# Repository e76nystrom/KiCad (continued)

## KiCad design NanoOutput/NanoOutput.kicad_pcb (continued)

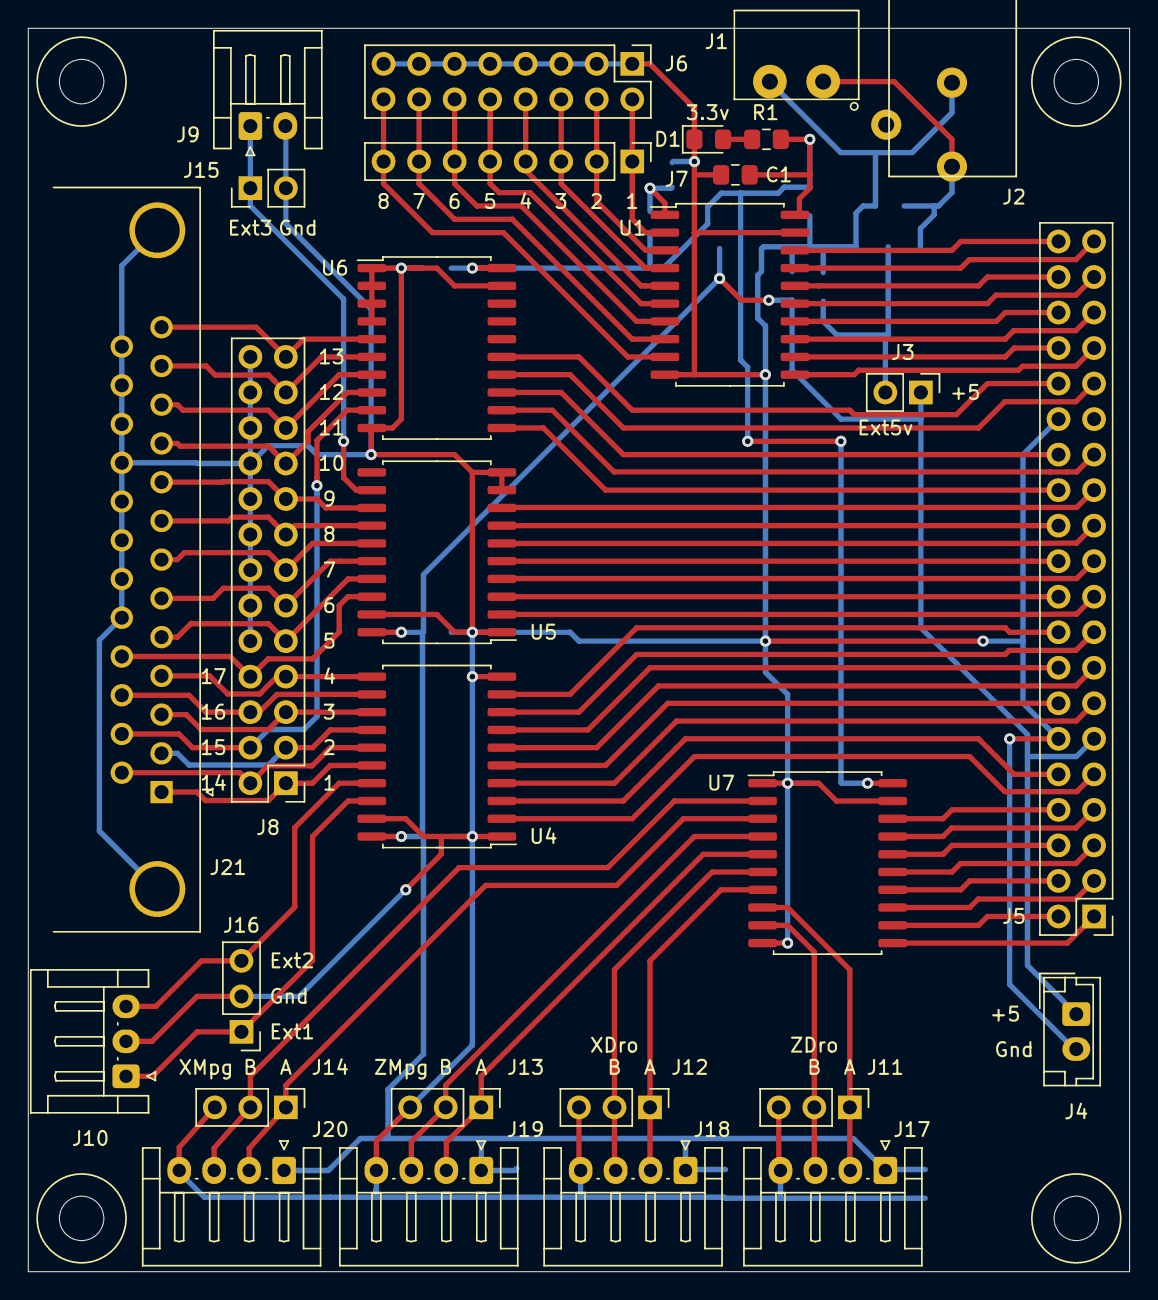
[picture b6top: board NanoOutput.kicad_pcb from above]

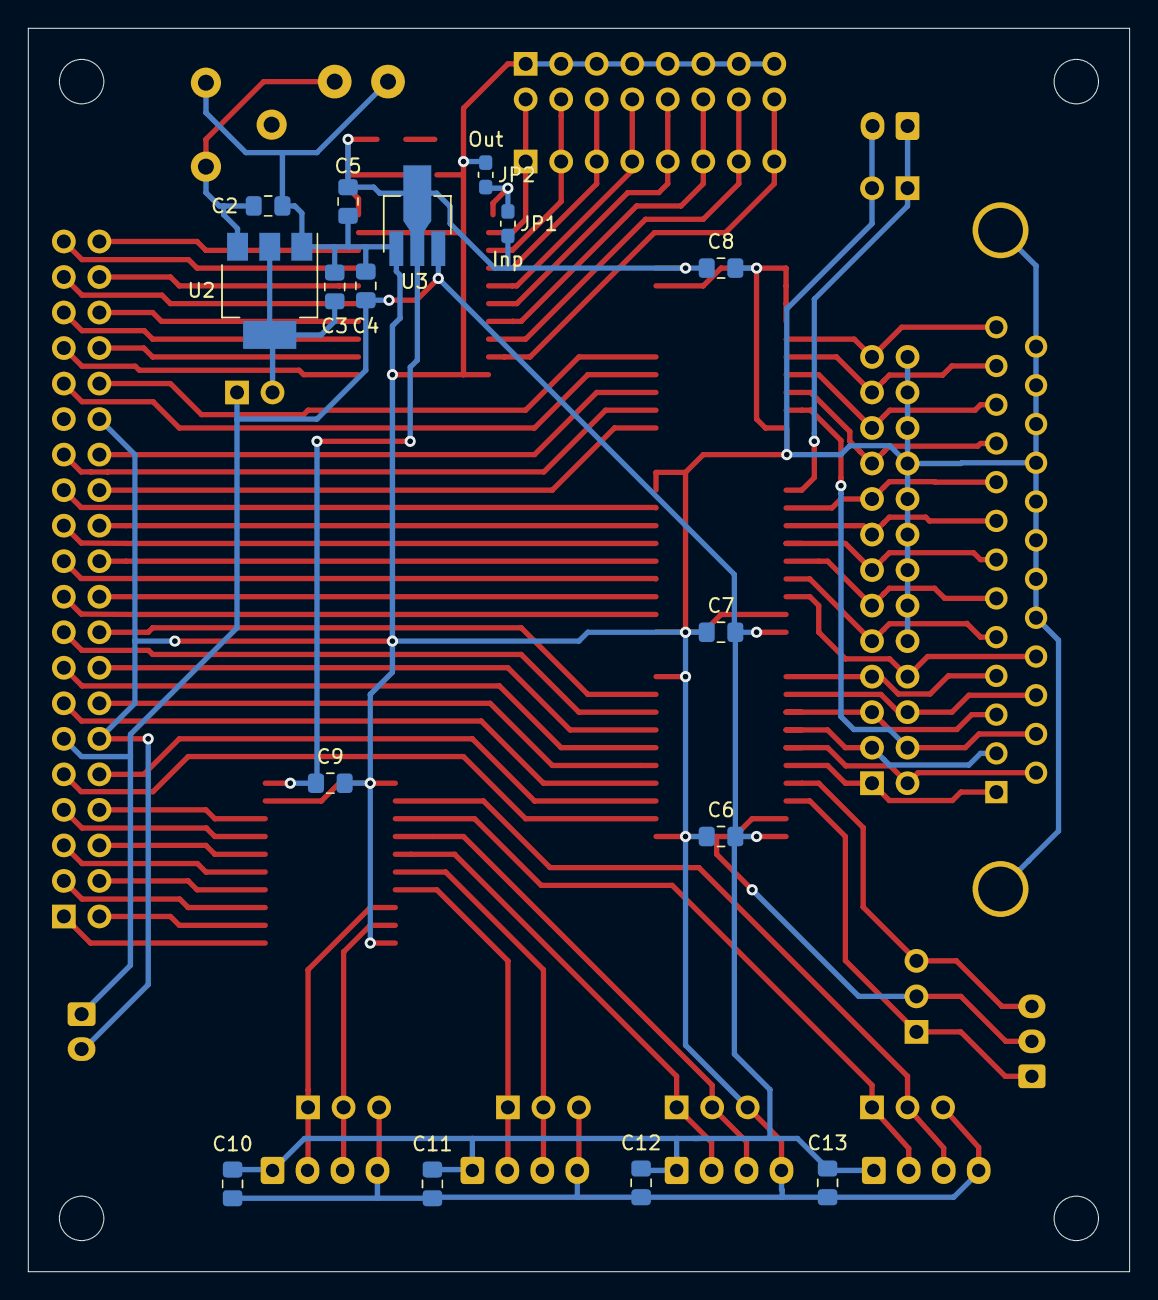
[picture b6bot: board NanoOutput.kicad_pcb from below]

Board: 2 copper layers, 78.7 x 88.9 mm, 49 parts (16 on the bottom side), 79 nets.

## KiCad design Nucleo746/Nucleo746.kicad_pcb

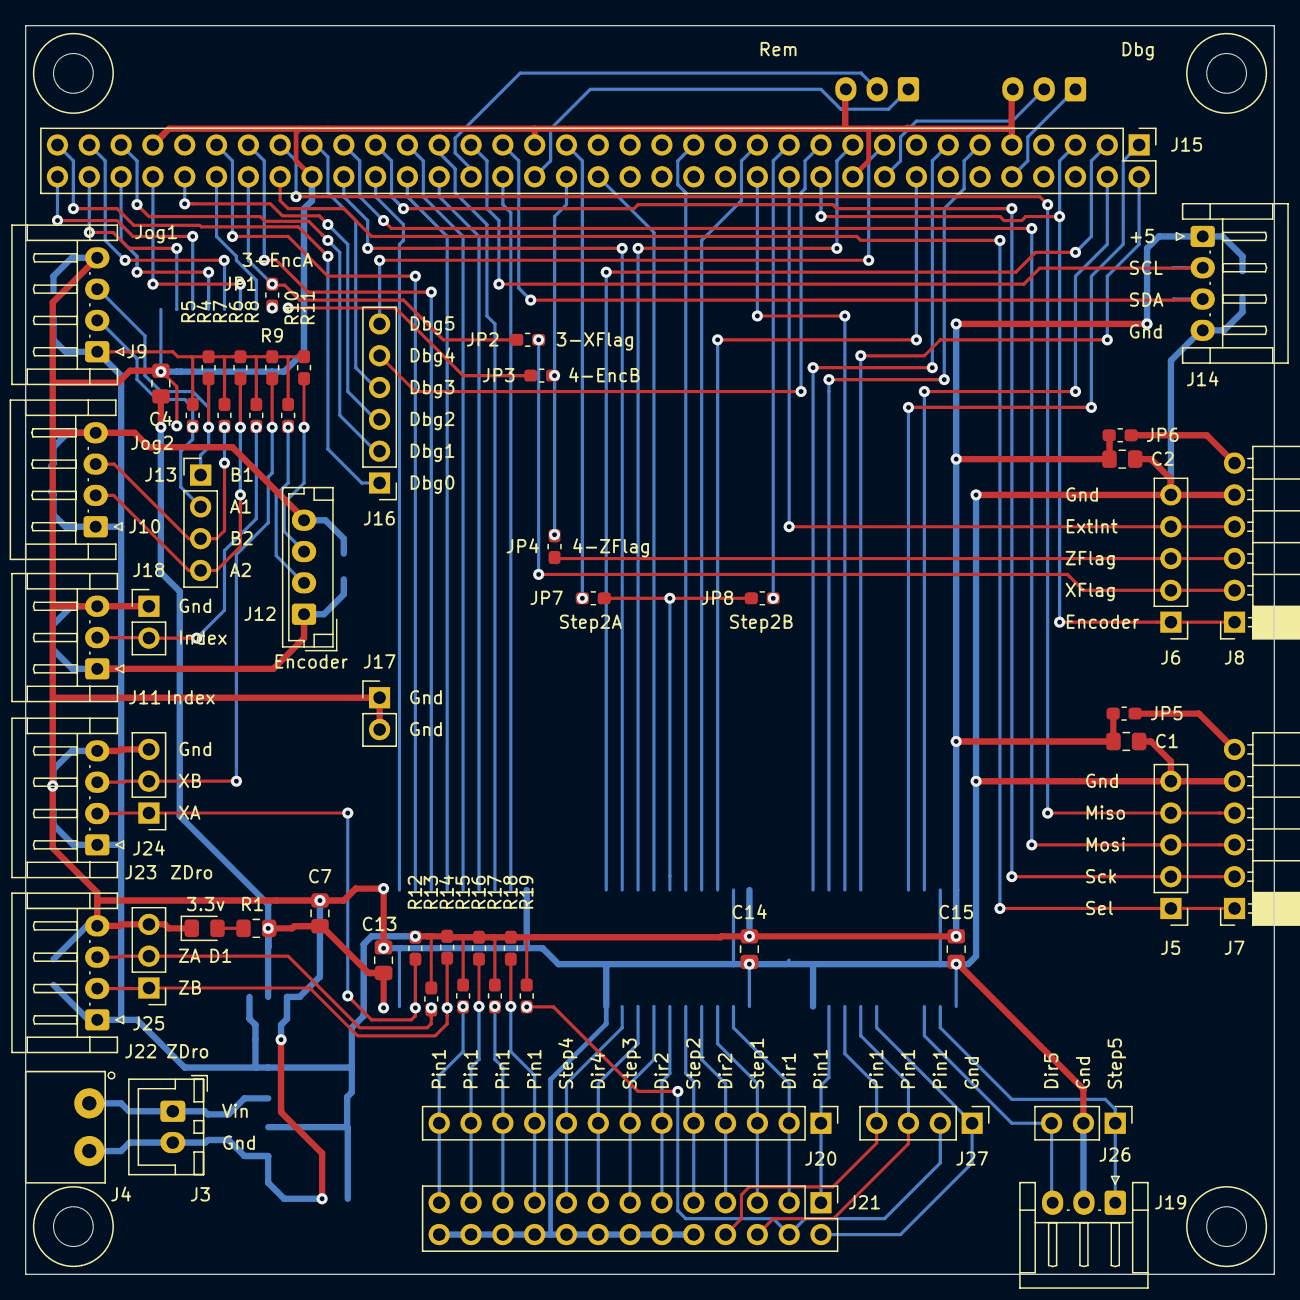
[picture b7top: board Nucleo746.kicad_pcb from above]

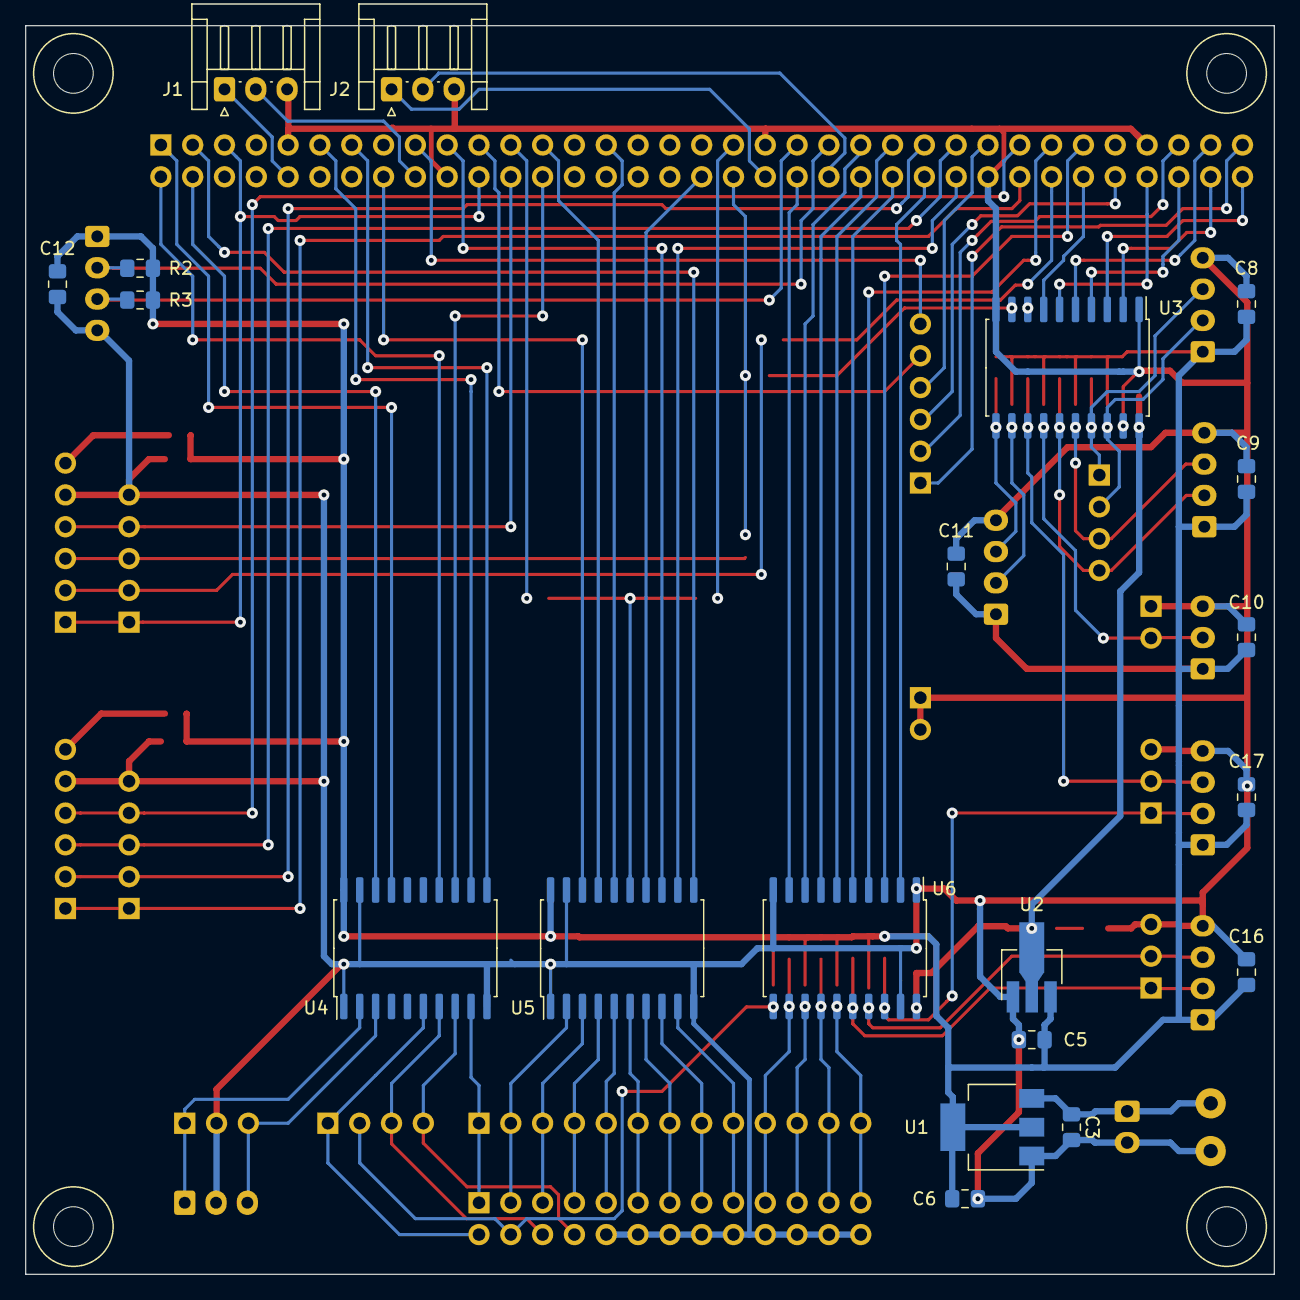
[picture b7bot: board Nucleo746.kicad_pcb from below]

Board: 2 copper layers, 99.7 x 99.7 mm, 82 parts (20 on the bottom side), 91 nets.

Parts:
C1, C2, C3, C4, C6, C8, C9, C10, C11, C12, C13, C14, C15, C16, C17: .1uf; C_0805_2012Metric_Pad1.15x1.40mm_HandSolder
C5, C7: 10uf; C_0805_2012Metric_Pad1.15x1.40mm_HandSolder
D1: LED; D_0805_2012Metric_Pad1.15x1.40mm_HandSolder
H1, H2, H3, H4: MountingHole; MountingHole _1-8_1-4
J1, J2, J11, J19: Conn_01x03; JST_EH_S3B-EH_1x03_P2.50mm_Horizontal
J3: Conn_01x02; JST_XH_B2B-XH-A_1x02_P2.50mm_Vertical
J4: Conn_01x02; 2 Pin 3.81mm
J5, J6: Conn_01x05_Male; PinHeader_1x05_P2.54mm_Vertical
J7, J8: Conn_01x06; PinSocket_1x06_P2.54mm_Horizontal
J9, J10, J14, J22, J23: Conn_01x04; JST_EH_S4B-EH_1x04_P2.50mm_Horizontal
J12: Conn_01x04; JST_EH_B4B-EH-A_1x04_P2.50mm_Vertical
J13, J27: Conn_01x04_Male; PinHeader_1x04_P2.54mm_Vertical
J15: N746Right; PinHeader_2x35_P2.54mm_Vertical
J16: Conn_01x06_Male; PinHeader_1x06_P2.54mm_Vertical
J17, J18: Conn_01x02_Male; PinHeader_1x02_P2.54mm_Vertical
J20: Conn_01x13_Male; PinHeader_1x13_P2.54mm_Vertical
J21: Conn_02x13_Top_Bottom; PinHeader_2x13_P2.54mm_Vertical
J24, J25, J26: Conn_01x03_Male; PinHeader_1x03_P2.54mm_Vertical
JP1, JP3, JP7: S2_T5; R_0603_1608Metric_Pad1.05x0.95mm_HandSolder
JP2, JP4, JP8: S2_T1; R_0603_1608Metric_Pad1.05x0.95mm_HandSolder
JP5, JP6: 5v; R_0603_1608Metric_Pad1.05x0.95mm_HandSolder
R1: R; R_0805_2012Metric_Pad1.15x1.40mm_HandSolder
R2, R3: 4.7k; R_0805_2012Metric_Pad1.15x1.40mm_HandSolder
R4, R5, R6, R7, R8, R9, R10, R11, R12, R13, R14, R15, R16, R17, R18, R19: 10k; R_0603_1608Metric_Pad1.05x0.95mm_HandSolder
U1: AMS1117-5.0; SOT-223-3_TabPin2
U2: AMS1117-3.3; SOT-89-3_Handsoldering
U3, U4, U5, U6: 74HC245; SOIC-20W_7.5x12.8mm_P1.27mm

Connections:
+3V3: C4.1, C7.1, C13.1, R1.1, U2.2, U3.20, U6.20
+5V: C1.1, C2.1, C5.1, C6.1, C8.1, C9.1, C10.1, C11.1, C12.1, C14.1, C15.1, C16.1, C17.1, J9.1, J10.1, J11.1, J12.1, J14.1, J22.1, J23.1, JP5.1, JP6.1, R2.1, R3.1, R4.1, R5.1, R6.1, R7.1, R8.1, R9.1, R10.1, R11.1, R12.1, R13.1, R14.1, R15.1, R16.1, R17.1, R18.1, R19.1, U1.2, U2.3, U4.20, U5.20
/5v1: J7.6, JP5.2
/5v2: J8.6, JP6.2
/Dbg0: J15.69, J16.1
/Dbg1: J15.65, J16.2
/Dbg2: J15.62, J16.3
/Dbg3: J15.53, J16.4
/Dbg4: J15.21, J16.5
/Dbg5: J15.17, J16.6
/Dir1: J15.16, U5.18
/Dir1Buf: J20.2, J21.2, U5.2
/Dir2: J15.29, U5.16
/Dir2Buf: J20.4, J21.4, U5.4
/Dir3: J15.36, U5.14
/Dir3Buf: J20.6, J21.6, U5.6
/Dir4: J15.52, U5.12
/Dir4Buf: J20.8, J21.8, U5.8
/Dir5: J15.1, U4.17
/Dir5Buf: J19.3, J26.3, U4.3
/EncA: J12.2, R10.2, U3.12
/EncABuf: JP1.1, U3.8
/EncB: J12.3, R11.2, U3.11
/EncBBuf: JP3.1, U3.9
/Encoder: J6.1, J8.1, J15.5, J15.22
/ExtInt: J6.4, J8.4, J15.24
/Exti3: J15.58, JP1.2, JP2.1
/Exti4: J15.38, JP3.2, JP4.1
/I2C_SCL: J14.2, J15.43, R2.2
/I2C_SDA: J14.3, J15.41, R3.2
/Index: J11.2, J18.2, R8.2, U3.14
/IndexBuf: J15.64, U3.6
/JogA1: J9.2, J13.2, R5.2, U3.18
/JogA1Buf: J15.68, U3.2
/JogA2: J10.2, J13.4, R6.2, U3.15
/JogA2Buf: J15.67, U3.5
/JogB1: J9.3, J13.1, R4.2, U3.17
/JogB1Buf: J15.70, U3.3
/JogB2: J10.3, J13.3, R7.2, U3.16
/JogB2Buf: J15.66, U3.4
/LedR: D1.2, R1.2
/Pin1: J15.13, U4.11
/Pin1Buf: J20.1, J21.1, U4.9
/Pin10: J20.10, J21.10, R18.2, U6.12
/Pin10Buf: J15.45, U6.8
/Pin11: J20.11, J21.11, R17.2, U6.13
/Pin11Buf: J15.46, U6.7
/Pin12: J20.12, J21.12, R16.2, U6.14
/Pin12Buf: J15.47, U6.6
/Pin13: J20.13, J21.13, R15.2, U6.15
/Pin13Buf: J15.48, U6.5
/Pin14: J15.2, U4.14
/Pin14Buf: J21.14, J27.1, U4.6
/Pin15: J21.15, J27.2, R19.2, U6.11
/Pin15Buf: J15.42, U6.9
/Pin16Buf: J21.16, J27.3, U4.7
/Pin17: J15.11, U4.12
/Pin17Buf: J21.17, J27.4, U4.8
/Pwm: J15.26, U4.13
/SPI_MISO: J5.4, J7.4, J15.55
/SPI_MOSI: J5.3, J7.3, J15.51
/SPI_SCK: J5.2, J7.2, J15.49
/SPI_SEL: J5.1, J7.1, J15.56
/Step1: J15.25, U5.17
/Step1Buf: J20.3, J21.3, U5.3
/Step2: JP7.2, JP8.1, U5.15
/Step2A: J15.37, JP7.1
/Step2B: J15.23, JP8.2
/Step2Buf: J20.5, J21.5, U5.5
/Step3: J15.19, U5.13
/Step3Buf: J20.7, J21.7, U5.7
/Step4: J15.3, U5.11
/Step4Buf: J20.9, J21.9, U5.9
/Step5: J15.4, U4.18
/Step5Buf: J19.1, J26.1, U4.2
/Uart3Rx: J1.2, J15.18
/Uart3Tx: J1.1, J15.10
/Uart7Rx: J2.2, J15.44
/Uart7Tx: J2.1, J15.40
/Vin: C3.1, J3.1, J4.1, U1.3
/XA: J23.2, J24.1, R12.2, U6.18
/XABuf: J15.50, U6.2
/XB: J23.3, J24.2, R9.2, U3.13
/XBBuf: J15.60, U3.7
/XFlag: J6.2, J8.2, JP2.2
/ZA: J22.2, J25.1, R14.2, U6.16
/ZABuf: J15.59, U6.3
/ZB: J22.3, J25.2, R13.2, U6.17
/ZBBuf: J15.57, U6.4
/ZFlag: J6.3, J8.3, JP4.2
GND: C1.2, C2.2, C3.2, C4.2, C5.2, C6.2, C7.2, C8.2, C9.2, C10.2, C11.2, C12.2, C13.2, C14.2, C15.2, C16.2, C17.2, D1.1, J1.3, J2.3, J3.2, J4.2, J5.5, J6.5, J7.5, J8.5, J9.4, J10.4, J11.3, J12.4, J14.4, J15.9, J15.20, J15.39, J15.54, J15.63, J17.1, J17.2, J18.1, J19.2, J21.18, J21.19, J21.20, J21.21, J21.22, J21.23, J21.24, J21.25, J21.26, J22.4, J23.4, J24.3, J25.3, J26.2, U1.1, U2.1, U3.1, U3.10, U3.19, U4.1, U4.10, U4.19, U5.1, U5.10, U5.19, U6.1, U6.10, U6.19

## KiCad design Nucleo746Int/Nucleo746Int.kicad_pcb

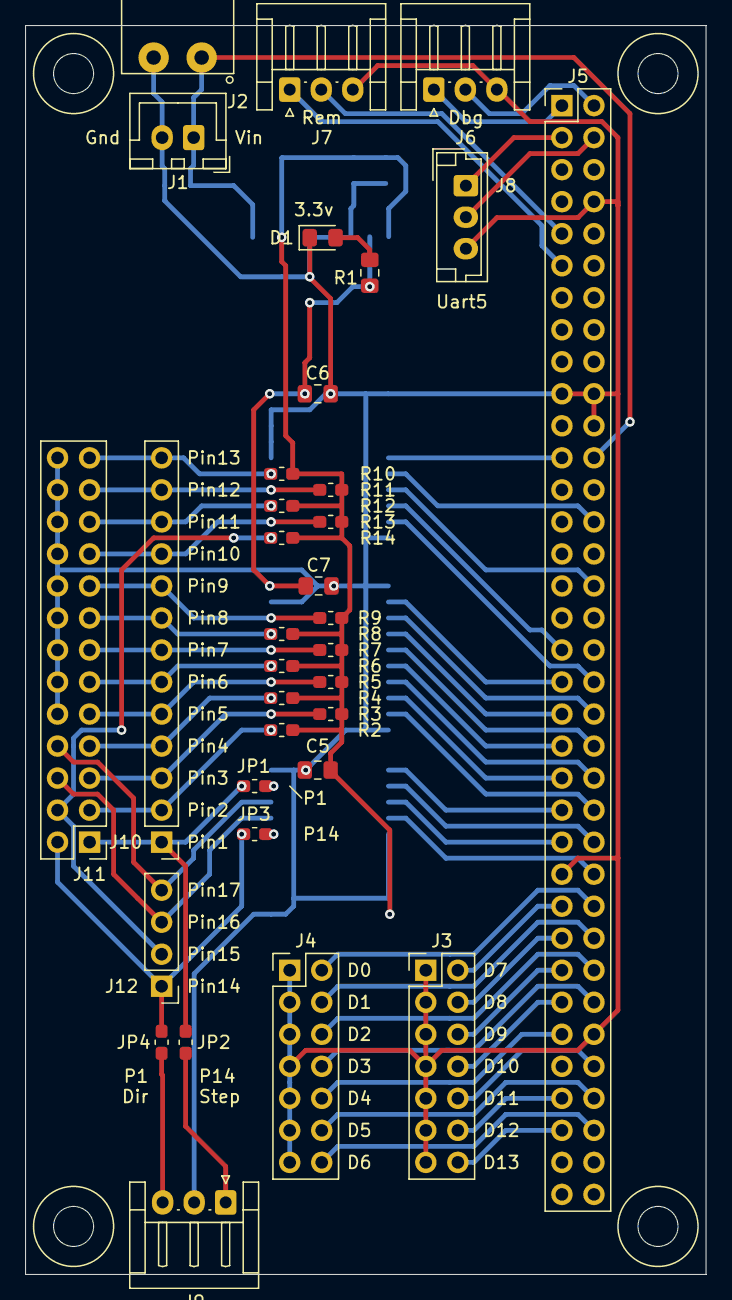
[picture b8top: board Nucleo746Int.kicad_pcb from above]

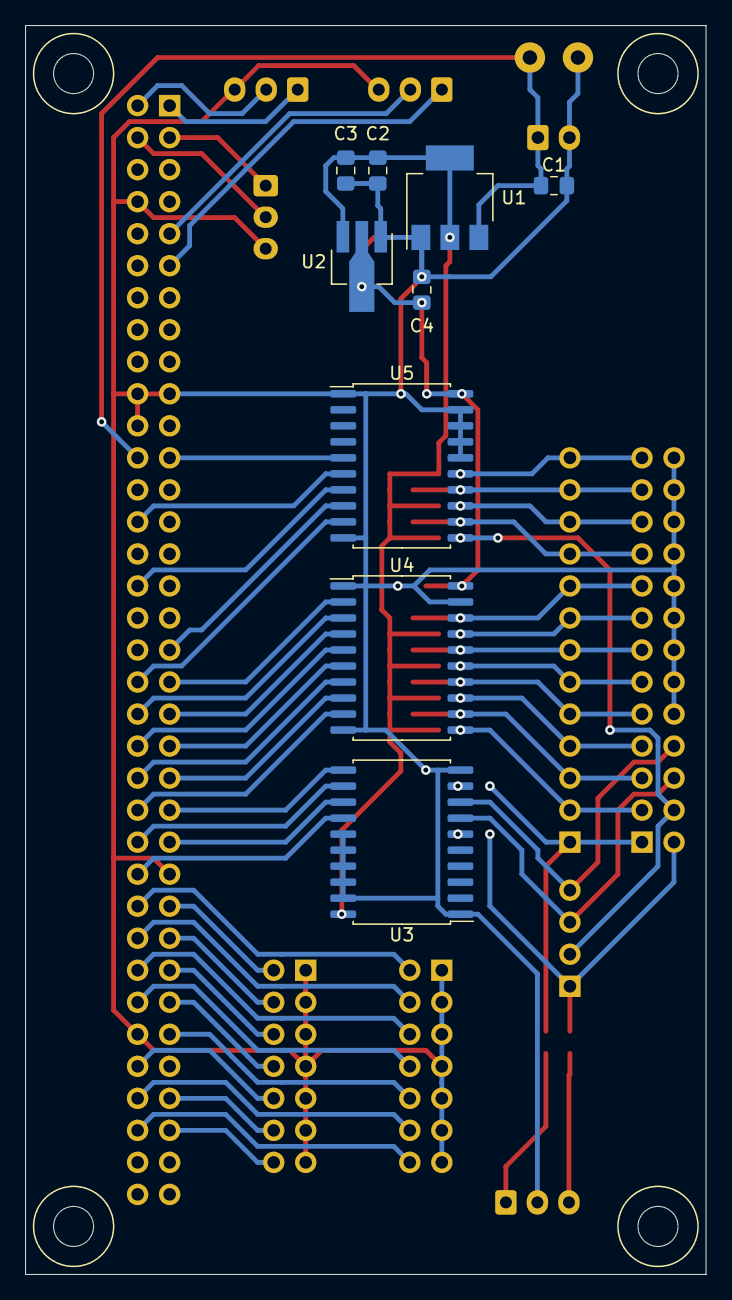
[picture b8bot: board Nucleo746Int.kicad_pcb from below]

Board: 2 copper layers, 54.0 x 99.1 mm, 47 parts (9 on the bottom side), 63 nets.

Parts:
C1, C3, C5, C6, C7: .1uf; C_0805_2012Metric_Pad1.15x1.40mm_HandSolder
C2, C4: 10uf; C_0805_2012Metric_Pad1.15x1.40mm_HandSolder
D1: LED; D_0805_2012Metric_Pad1.15x1.40mm_HandSolder
H1, H2, H3, H4: MountingHole; MountingHole _1-8_1-4
J1: Conn_01x02; JST_XH_B2B-XH-A_1x02_P2.50mm_Vertical
J2: Conn_01x02; 2 Pin 3.81mm
J3, J4: Conn_02x07_Odd_Even; PinHeader_2x07_P2.54mm_Vertical
J5: N746Left; PinHeader_2x35_P2.54mm_Vertical
J6, J7, J9: Conn_01x03; JST_EH_S3B-EH_1x03_P2.50mm_Horizontal
J8: Conn_01x03; JST_EH_B3B-EH-A_1x03_P2.50mm_Vertical
J10: Conn_01x13_Male; PinHeader_1x13_P2.54mm_Vertical
J11: Conn_02x13_Top_Bottom; PinHeader_2x13_P2.54mm_Vertical
J12: Conn_01x04_Male; PinHeader_1x04_P2.54mm_Vertical
JP1, JP2, JP3, JP4: Jumper_NO_Small; R_0603_1608Metric_Pad1.05x0.95mm_HandSolder
R1: R; R_0805_2012Metric_Pad1.15x1.40mm_HandSolder
R2, R3, R4, R5, R6, R7, R8, R9, R10, R11, R12, R13, R14: 10k; R_0603_1608Metric_Pad1.05x0.95mm_HandSolder
U1: AMS1117-5.0; SOT-223-3_TabPin2
U2: AMS1117-3.3; SOT-89-3_Handsoldering
U3, U4, U5: 74HC245; SOIC-20W_7.5x12.8mm_P1.27mm

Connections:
+3V3: C4.1, C6.1, C7.1, R1.1, U2.2, U4.20, U5.20
+5V: C2.1, C3.1, C5.1, R2.1, R3.1, R4.1, R5.1, R6.1, R7.1, R8.1, R9.1, R10.1, R11.1, R12.1, R13.1, R14.1, U1.2, U2.3, U3.20
/DbgA0: J4.2, J5.52
/DbgA1: J4.4, J5.54
/DbgA2: J4.6, J5.56
/DbgA3: J4.8, J5.58
/DbgA4: J4.10, J5.59
/DbgA5: J4.12, J5.64
/DbgA6: J4.14, J5.66
/DbgA7: J3.2, J5.51
/DbgA8: J3.4, J5.53
/DbgA9: J3.6, J5.55
/DbgA10: J3.8, J5.57
/DbgA11: J3.10, J5.62
/DbgA12: J3.12, J5.63
/DbgA13: J3.14, J5.65
/DirIn: J9.3, JP4.1
/LedR: D1.2, R1.2
/Pin1: J5.45, U3.11
/Pin1Buf: JP1.1, U3.9
/Pin1Out: J10.1, J11.1, JP1.2, JP2.2
/Pin2: J10.2, J11.2, R2.2, U4.11
/Pin2Buf: J5.46, U4.9
/Pin3: J10.3, J11.3, R3.2, U4.12
/Pin3Buf: J5.43, U4.8
/Pin4: J10.4, J11.4, R4.2, U4.13
/Pin4Buf: J5.44, U4.7
/Pin5: J10.5, J11.5, R5.2, U4.14
/Pin5Buf: J5.41, U4.6
/Pin6: J10.6, J11.6, R6.2, U4.15
/Pin6Buf: J5.42, U4.5
/Pin7: J10.7, J11.7, R7.2, U4.16
/Pin7Buf: J5.39, U4.4
/Pin8: J10.8, J11.8, R8.2, U4.17
/Pin8Buf: J5.40, U4.3
/Pin9: J10.9, J11.9, R9.2, U4.18
/Pin9Buf: J5.37, U4.2
/Pin10: J10.10, J11.10, R13.2, U5.12
/Pin10Buf: J5.35, U5.8
/Pin11: J10.11, J11.11, R12.2, U5.13
/Pin11Buf: J5.32, U5.7
/Pin12: J10.12, J11.12, R11.2, U5.14
/Pin12Buf: J5.28, U5.6
/Pin13: J10.13, J11.13, R10.2, U5.15
/Pin13Buf: J5.23, U5.5
/Pin14: J5.50, U3.14
/Pin14Buf: JP3.1, U3.6
/Pin14Out: J11.14, J12.1, JP3.2, JP4.2
/Pin15: J11.15, J12.2, R14.2, U5.11
/Pin15Buf: J5.38, U5.9
/Pin16: J5.47, U3.13
/Pin16Buf: J11.16, J12.3, U3.7
/Pin17: J5.48, U3.12
/Pin17Buf: J11.17, J12.4, U3.8
/StepIn: J9.1, JP2.1
/Uart3Rx: J5.2, J6.2
/Uart3Tx: J5.1, J6.1
/Uart5Rx: J5.4, J8.2
/Uart5Tx: J5.3, J8.1
/Uart7Rx: J5.9, J7.2
/Uart7Tx: J5.11, J7.1
/Vin: C1.1, J1.1, J2.1, J5.24, U1.3
GND: C1.2, C2.2, C3.2, C4.2, C5.2, C6.2, C7.2, D1.1, J1.2, J2.2, J3.1, J3.3, J3.5, J3.7, J3.9, J3.11, J3.13, J4.1, J4.3, J4.5, J4.7, J4.9, J4.11, J4.13, J5.8, J5.19, J5.20, J5.22, J5.49, J5.60, J6.3, J7.3, J8.3, J9.2, J11.18, J11.19, J11.20, J11.21, J11.22, J11.23, J11.24, J11.25, J11.26, U1.1, U2.1, U3.1, U3.10, U3.15, U3.16, U3.17, U3.18, U3.19, U4.1, U4.10, U4.19, U5.1, U5.10, U5.16, U5.17, U5.18, U5.19
